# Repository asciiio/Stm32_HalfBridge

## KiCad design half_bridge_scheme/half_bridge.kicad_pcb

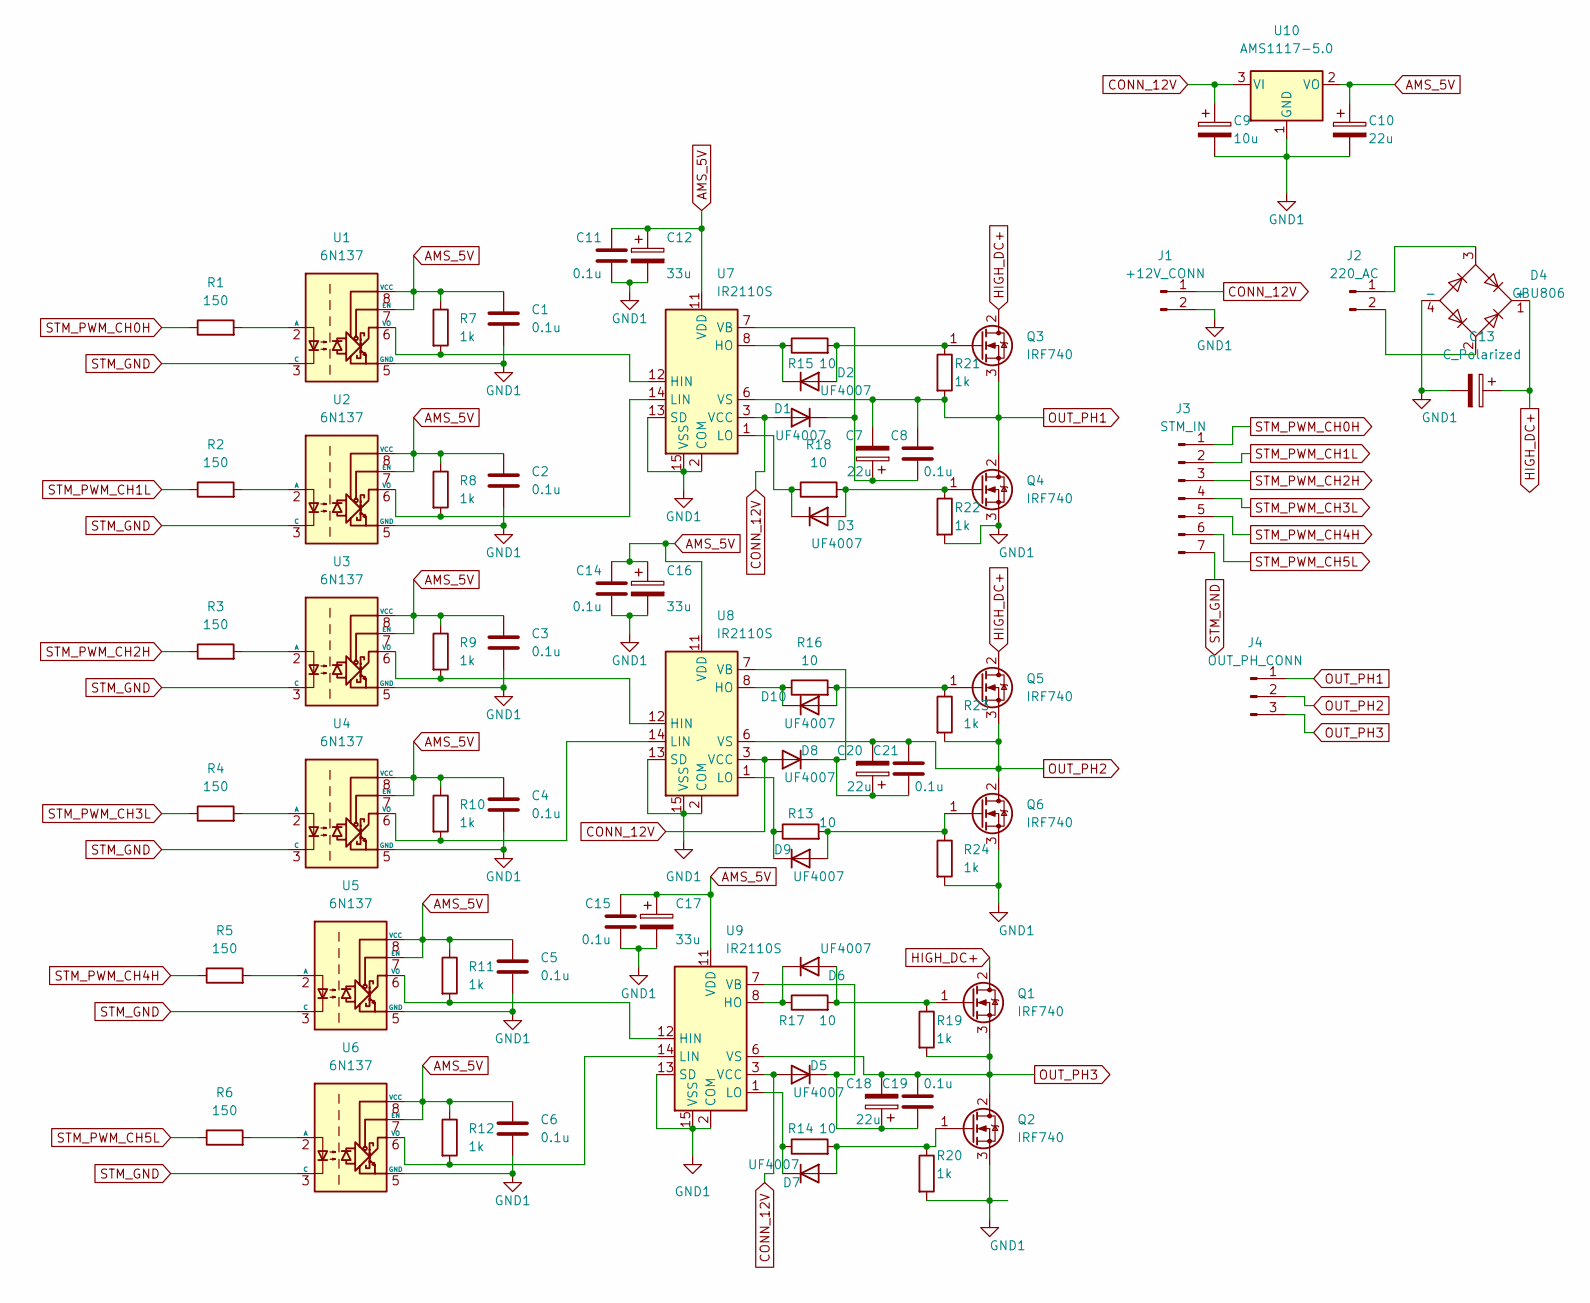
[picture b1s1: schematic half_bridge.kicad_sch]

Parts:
C1, C2, C3, C4, C5, C6, C8, C11, C14, C15, C19, C21: 0.1u; C_Disc_D4.3mm_W1.9mm_P5.00mm
C7, C10, C18, C20: 22u; CP_Radial_D5.0mm_P2.00mm
C9: 10u; CP_Radial_D5.0mm_P2.00mm
C12, C16, C17: 33u; CP_Radial_D5.0mm_P2.00mm
C13: C_Polarized; CP_Radial_D25.0mm_P10.00mm_SnapIn
D1, D2, D3, D5, D6, D7, D8, D9, D10: UF4007; D_DO-34_SOD68_P10.16mm_Horizontal
D4: GBU806; Diode_Bridge_Vishay_GBU
J1: +12V_CONN; 12v_CONN
J2: 220_AC; conn_220
J3: STM_IN; CONN1x7
J4: OUT_PH_CONN; PHASE_3_OUT
Q1, Q2, Q3, Q4, Q5, Q6: IRF740; TO-220-3_Vertical
R1, R2, R3, R4, R5, R6: 150; R_0603_1608Metric
R7, R8, R9, R10, R11, R12: 1k; R_0603_1608Metric
R13, R14, R15, R16, R17, R18: 10; R_0603_1608Metric
R19, R20, R21, R22, R23, R24: 1k; R_Axial_DIN0207_L6.3mm_D2.5mm_P10.16mm_Horizontal
U1, U2, U3, U4, U5, U6: 6N137; DIP-8_W7.62mm
U7, U8, U9: IR2110S; SOIC-16W_7.5x10.3mm_P1.27mm
U10: AMS1117-5.0; SOT-223-3_TabPin2

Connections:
AMS_5V: C1.1, C2.1, C3.1, C4.1, C5.1, C6.1, C10.1, C11.2, C12.1, C14.2, C15.2, C16.1, C17.1, R7.1, R8.1, R9.1, R10.1, R11.1, R12.1, U1.7 (EN), U1.8 (VCC), U2.7 (EN), U2.8 (VCC), U3.7 (EN), U3.8 (VCC), U4.7 (EN), U4.8 (VCC), U5.7 (EN), U5.8 (VCC), U6.7 (EN), U6.8 (VCC), U7.11 (VDD), U8.11 (VDD), U9.11 (VDD), U10.2 (VO)
CONN_12V: C9.1, D1.2 (A), D5.2 (A), D8.2 (A), J1.1, U7.3 (VCC), U8.3 (VCC), U9.3 (VCC), U10.3 (VI)
GND1: C1.2, C2.2, C3.2, C4.2, C5.2, C6.2, C9.2, C10.2, C11.1, C12.2, C13.2, C14.1, C15.1, C16.2, C17.2, D4.4 (-), J1.2, Q2.3 (S), Q4.3 (S), Q6.3 (S), R20.2, R22.2, R24.2, U1.5 (GND), U2.5 (GND), U3.5 (GND), U4.5 (GND), U5.5 (GND), U6.5 (GND), U7.2 (COM), U7.13 (SD), U7.15 (VSS), U8.2 (COM), U8.13 (SD), U8.15 (VSS), U9.2 (COM), U9.13 (SD), U9.15 (VSS), U10.1 (GND)
HIGH_DC+: C13.1, D4.1 (+), Q1.2 (D), Q3.2 (D), Q5.2 (D)
unnamed: C7.1, C8.1, D1.1 (K), U7.7 (VB)
unnamed: C18.1, C19.1, D5.1 (K), U9.7 (VB)
unnamed: C20.1, C21.1, D8.1 (K), U8.7 (VB)
unnamed: D2.1 (K), R15.1, U7.8 (HO)
unnamed: D2.2 (A), Q3.1 (G), R15.2, R21.1
unnamed: D3.1 (K), R18.1, U7.1 (LO)
unnamed: D3.2 (A), Q4.1 (G), R18.2, R22.1
unnamed: D4.2, J2.2
unnamed: D4.3, J2.1
unnamed: D6.1 (K), R17.1, U9.8 (HO)
unnamed: D6.2 (A), Q1.1 (G), R17.2, R19.1
unnamed: D7.1 (K), R14.1, U9.1 (LO)
unnamed: D7.2 (A), Q2.1 (G), R14.2, R20.1
unnamed: D9.1 (K), R13.1, U8.1 (LO)
unnamed: D9.2 (A), Q6.1 (G), R13.2, R24.1
unnamed: D10.1 (K), R16.1, U8.8 (HO)
unnamed: D10.2 (A), Q5.1 (G), R16.2, R23.1
unnamed: R1.2, U1.2 (A)
unnamed: R2.2, U2.2 (A)
unnamed: R3.2, U3.2 (A)
unnamed: R4.2, U4.2 (A)
unnamed: R5.2, U5.2 (A)
unnamed: R6.2, U6.2 (A)
unnamed: R7.2, U1.6 (VO), U7.12 (HIN)
unnamed: R8.2, U2.6 (VO), U7.14 (LIN)
unnamed: R9.2, U3.6 (VO), U8.12 (HIN)
unnamed: R10.2, U4.6 (VO), U8.14 (LIN)
unnamed: R11.2, U5.6 (VO), U9.12 (HIN)
unnamed: R12.2, U6.6 (VO), U9.14 (LIN)
OUT_PH1: C7.2, C8.2, J4.1, Q3.3 (S), Q4.2 (D), R21.2, U7.6 (VS)
OUT_PH2: C20.2, C21.2, J4.2, Q5.3 (S), Q6.2 (D), R23.2, U8.6 (VS)
OUT_PH3: C18.2, C19.2, J4.3, Q1.3 (S), Q2.2 (D), R19.2, U9.6 (VS)
STM_GND: J3.7, U1.3 (C), U2.3 (C), U3.3 (C), U4.3 (C), U5.3 (C), U6.3 (C)
STM_PWM_CH0H: J3.1, R1.1
STM_PWM_CH1L: J3.2, R2.1
STM_PWM_CH2H: J3.3, R3.1
STM_PWM_CH3L: J3.4, R4.1
STM_PWM_CH4H: J3.5, R5.1
STM_PWM_CH5L: J3.6, R6.1

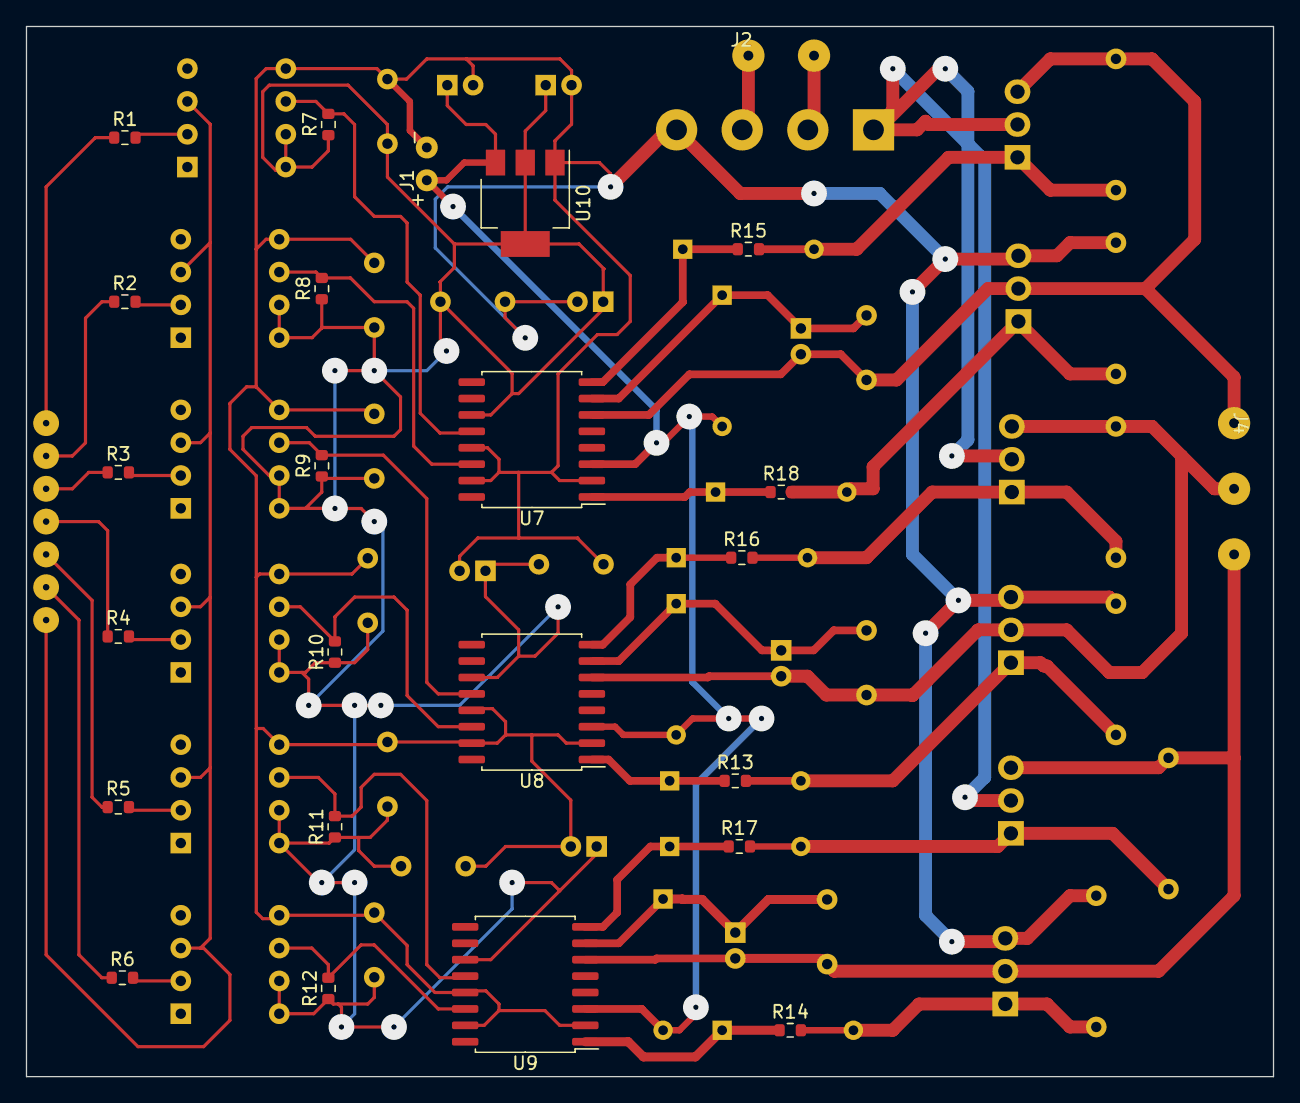
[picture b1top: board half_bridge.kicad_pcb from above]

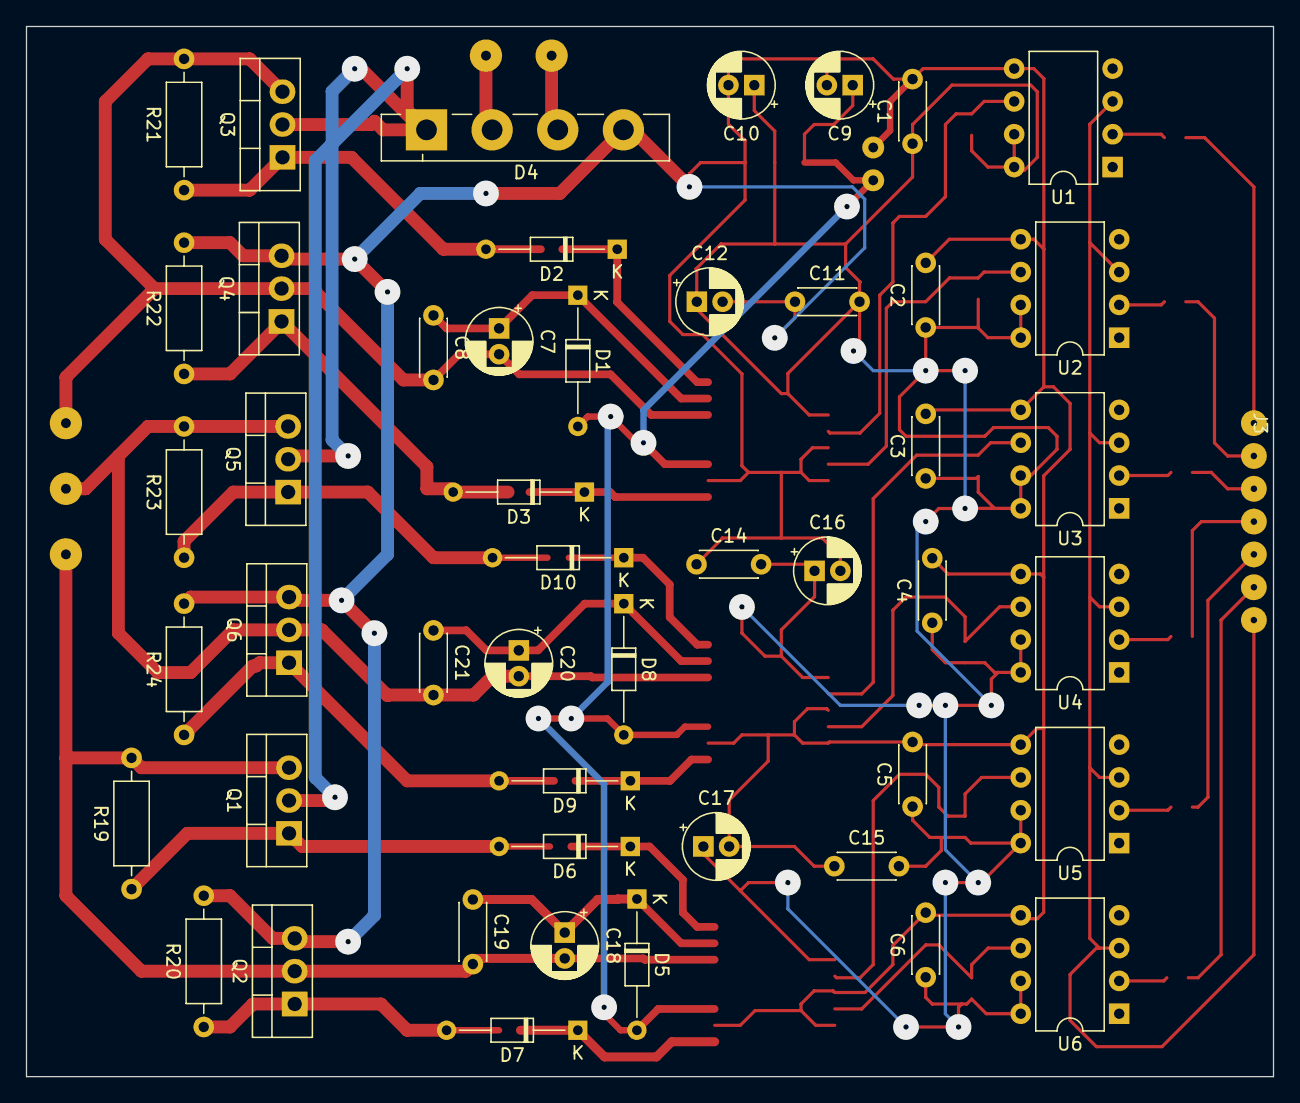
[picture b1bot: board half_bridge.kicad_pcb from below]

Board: 2 copper layers, 96.5 x 81.3 mm, 74 parts (49 on the bottom side), 43 nets.

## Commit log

2026-06-28 add schematic
2026-06-28 add qt app
